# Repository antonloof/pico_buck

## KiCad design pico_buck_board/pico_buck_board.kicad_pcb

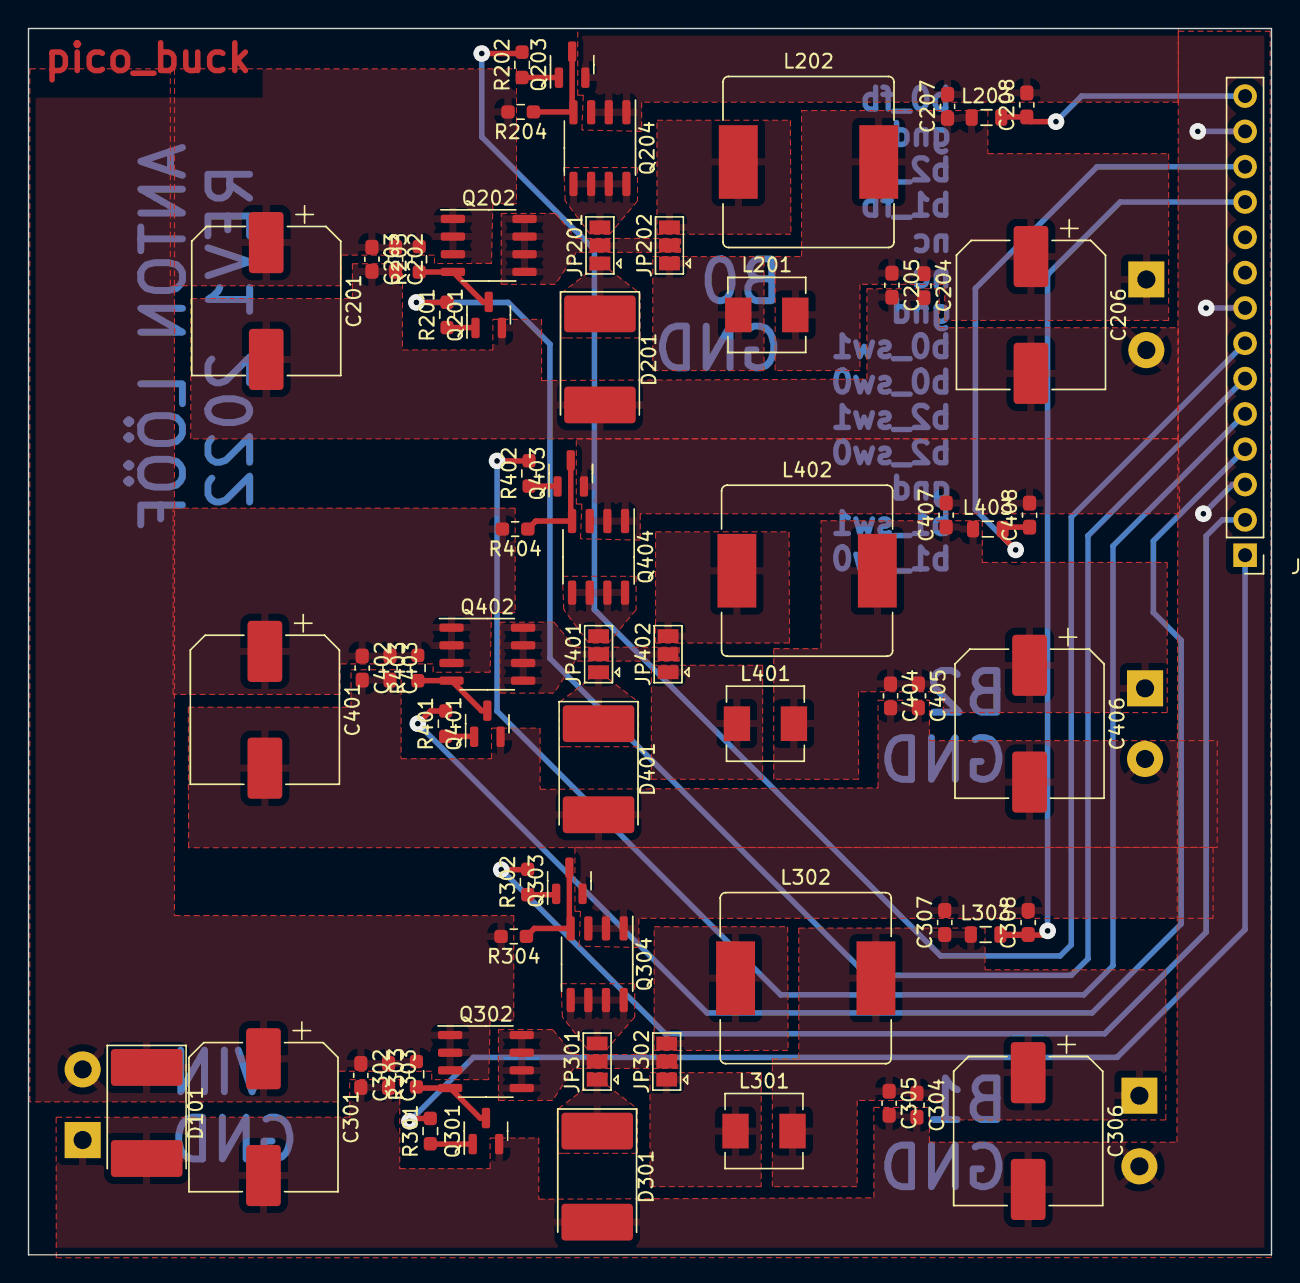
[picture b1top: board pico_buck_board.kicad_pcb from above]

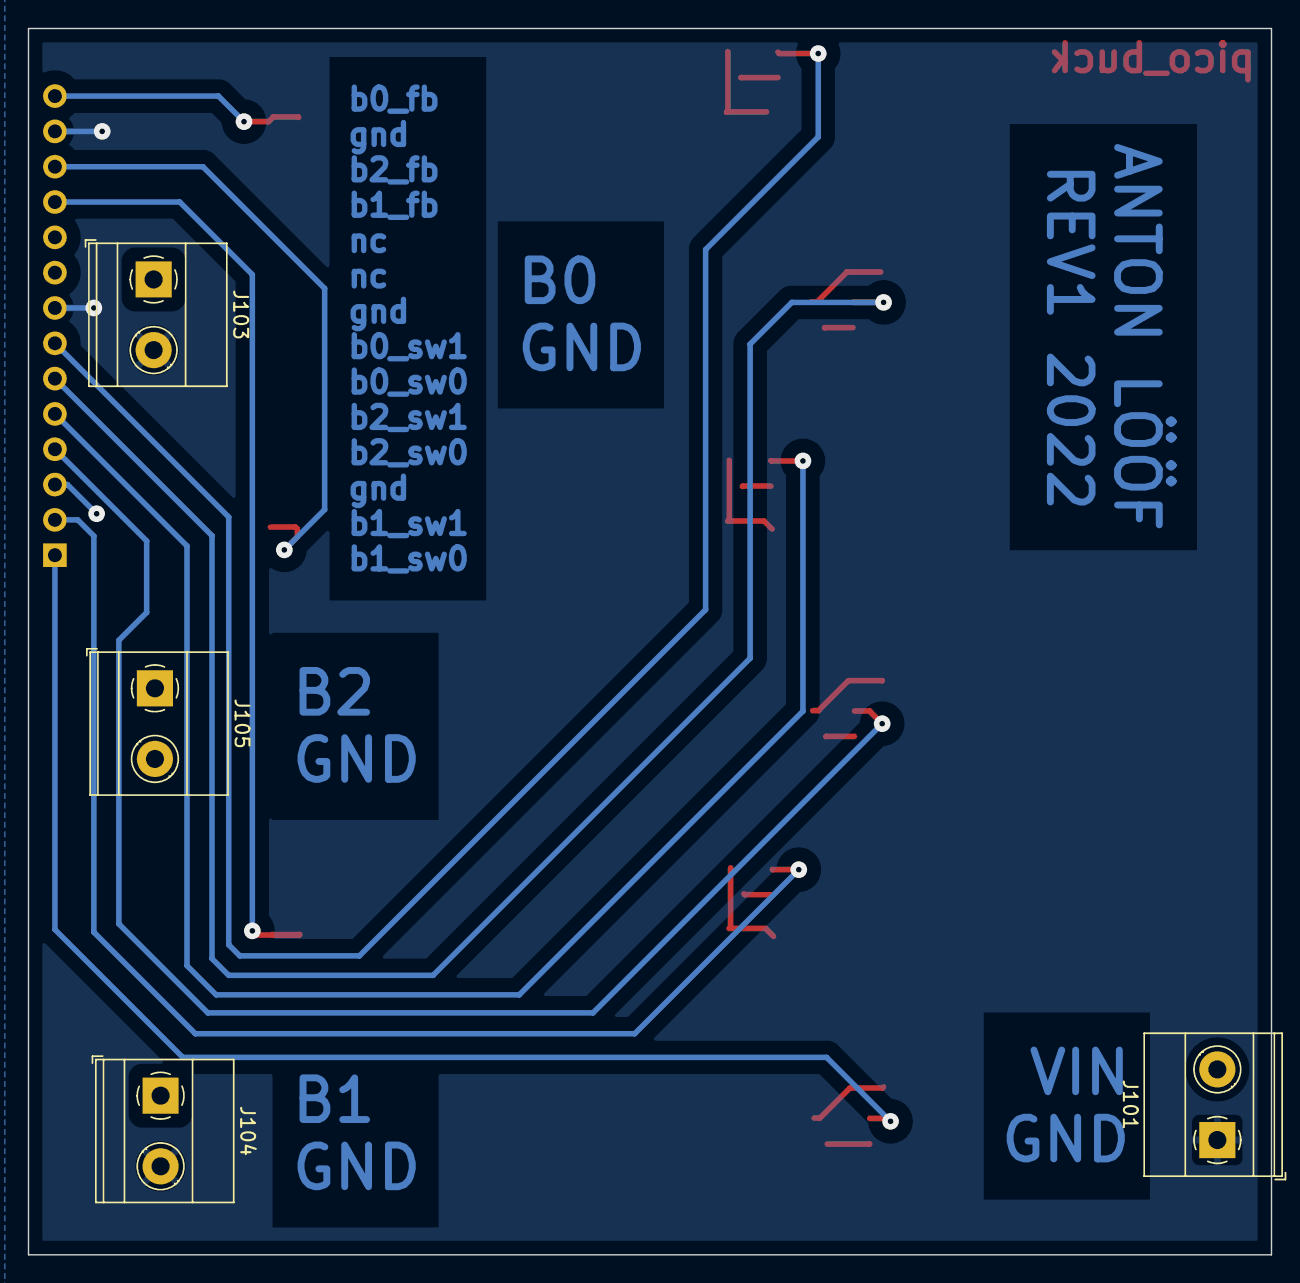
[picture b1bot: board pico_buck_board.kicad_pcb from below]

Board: 2 copper layers, 89.4 x 88.2 mm, 72 parts (4 on the bottom side), 41 nets.

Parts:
C201, C206, C301, C306, C401, C406: 470u; CP_Elec_10x10.5
C202, C203, C204, C205, C302, C303, C304, C305, C402, C403, C404, C405: 22u; C_0603_1608Metric_Pad1.08x0.95mm_HandSolder
C207, C208, C307, C308, C407, C408: 1u; C_0603_1608Metric_Pad1.08x0.95mm_HandSolder
D101, D201, D301, D401: PJON GGE; D_3220_8050Metric_Pad2.65x5.15mm_HandSolder
J101, J103, J104, J105: Conn_01x02; TerminalBlock_Phoenix_MKDS-1,5-2-5.08_1x02_P5.08mm_Horizont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
J102: part_of_pico; PinHeader_1x14_P2.54mm_Vertical
JP201, JP202, JP301, JP302, JP401, JP402: SolderJumper_3_Open; SolderJumper-3_P1.3mm_Open_Pad1.0x1.5mm
L201, L301, L401: 1u5; L_Sunlord_MWSA0518_5.4x5.2mm
L202, L302, L402: 10u; L_Bourns_SRR1210A
L203, L303, L403: 10u; L_0805_2012Metric
Q201, Q203, Q301, Q303, Q401, Q403: KST5551MTF; SOT-23
Q202, Q204, Q302, Q304, Q402, Q404: FSD4435; SO-8_3.9x4.9mm_P1.27mm
R201, R202, R301, R302, R401, R402: 1k; R_0603_1608Metric_Pad0.98x0.95mm_HandSolder
R203, R204, R303, R304, R403, R404: 10; R_0603_1608Metric_Pad0.98x0.95mm_HandSolder

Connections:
+5V: C201.1, C202.1, C203.1, C301.1, C302.1, C303.1, C401.1, C402.1, C403.1, D101.1 (K), J101.2, Q202.1 (S), Q202.2 (S), Q202.3 (S), Q302.1 (S), Q302.2 (S), Q302.3 (S), Q402.1 (S), Q402.2 (S), Q402.3 (S), R203.2, R204.2, R303.2, R304.2, R403.2, R404.2
/buck0_fb: C208.1, J102.14, L203.2
/buck0_out: C204.1, C205.1, C206.1, C207.1, J103.1, L201.2, L202.2, L203.1
/buck0_sw0: J102.6, R201.2
/buck0_sw1: J102.7, R202.2
/buck1_fb: C308.1, J102.11, L303.2
/buck1_out: C304.1, C305.1, C306.1, C307.1, J104.1, L301.2, L302.2, L303.1
/buck1_sw0: J102.1, R301.2
/buck1_sw1: J102.2, R302.2
/buck2_fb: C408.1, J102.12, L403.2
/buck2_out: C404.1, C405.1, C406.1, C407.1, J105.1, L401.2, L402.2, L403.1
/buck2_sw0: J102.4, R401.2
/buck2_sw1: J102.5, R402.2
/sync_buck1/sw0_gate: Q301.3 (C), Q302.4 (G), R303.1
/sync_buck1/sw1_gate: Q303.3 (C), Q304.4 (G), R304.1
/sync_buck1/swr0: Q301.1 (B), R301.1
/sync_buck1/swr1: Q303.1 (B), R302.1
/sync_buck1/vsw: JP301.2 (C), JP302.2 (C), Q302.5 (D), Q302.6 (D), Q302.7 (D), Q302.8 (D)
/sync_buck1/vsw_d: D301.1 (K), JP301.1 (A)
/sync_buck1/vsw_fet: JP301.3 (B), Q304.5 (D), Q304.6 (D), Q304.7 (D), Q304.8 (D)
/sync_buck1/vsw_lbig: JP302.3 (B), L302.1
/sync_buck1/vsw_lsmall: JP302.1 (A), L301.1
/sync_buck2/sw0_gate: Q401.3 (C), Q402.4 (G), R403.1
/sync_buck2/sw1_gate: Q403.3 (C), Q404.4 (G), R404.1
/sync_buck2/swr0: Q401.1 (B), R401.1
/sync_buck2/swr1: Q403.1 (B), R402.1
/sync_buck2/vsw: JP401.2 (C), JP402.2 (C), Q402.5 (D), Q402.6 (D), Q402.7 (D), Q402.8 (D)
/sync_buck2/vsw_d: D401.1 (K), JP401.1 (A)
/sync_buck2/vsw_fet: JP401.3 (B), Q404.5 (D), Q404.6 (D), Q404.7 (D), Q404.8 (D)
/sync_buck2/vsw_lbig: JP402.3 (B), L402.1
/sync_buck2/vsw_lsmall: JP402.1 (A), L401.1
/sync_buck/sw0_gate: Q201.3 (C), Q202.4 (G), R203.1
/sync_buck/sw1_gate: Q203.3 (C), Q204.4 (G), R204.1
/sync_buck/swr0: Q201.1 (B), R201.1
/sync_buck/swr1: Q203.1 (B), R202.1
/sync_buck/vsw: JP201.2 (C), JP202.2 (C), Q202.5 (D), Q202.6 (D), Q202.7 (D), Q202.8 (D)
/sync_buck/vsw_d: D201.1 (K), JP201.1 (A)
/sync_buck/vsw_fet: JP201.3 (B), Q204.5 (D), Q204.6 (D), Q204.7 (D), Q204.8 (D)
/sync_buck/vsw_lbig: JP202.3 (B), L202.1
/sync_buck/vsw_lsmall: JP202.1 (A), L201.1
GND: C201.2, C202.2, C203.2, C204.2, C205.2, C206.2, C207.2, C208.2, C301.2, C302.2, C303.2, C304.2, C305.2, C306.2, C307.2, C308.2, C401.2, C402.2, C403.2, C404.2, C405.2, C406.2, C407.2, C408.2, D101.2 (A), D201.2 (A), D301.2 (A), D401.2 (A), J101.1, J102.3, J102.8, J102.13, J103.2, J104.2, J105.2, Q201.2 (E), Q203.2 (E), Q204.1 (S), Q204.2 (S), Q204.3 (S), Q301.2 (E), Q303.2 (E), Q304.1 (S), Q304.2 (S), Q304.3 (S), Q401.2 (E), Q403.2 (E), Q404.1 (S), Q404.2 (S), Q404.3 (S)

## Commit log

2022-03-18 Add some schema, still need footprints
2022-03-20 add footprints
2022-03-20 some layoutin'
2022-03-25 rev1 board done
2022-03-27 add spwm sw
